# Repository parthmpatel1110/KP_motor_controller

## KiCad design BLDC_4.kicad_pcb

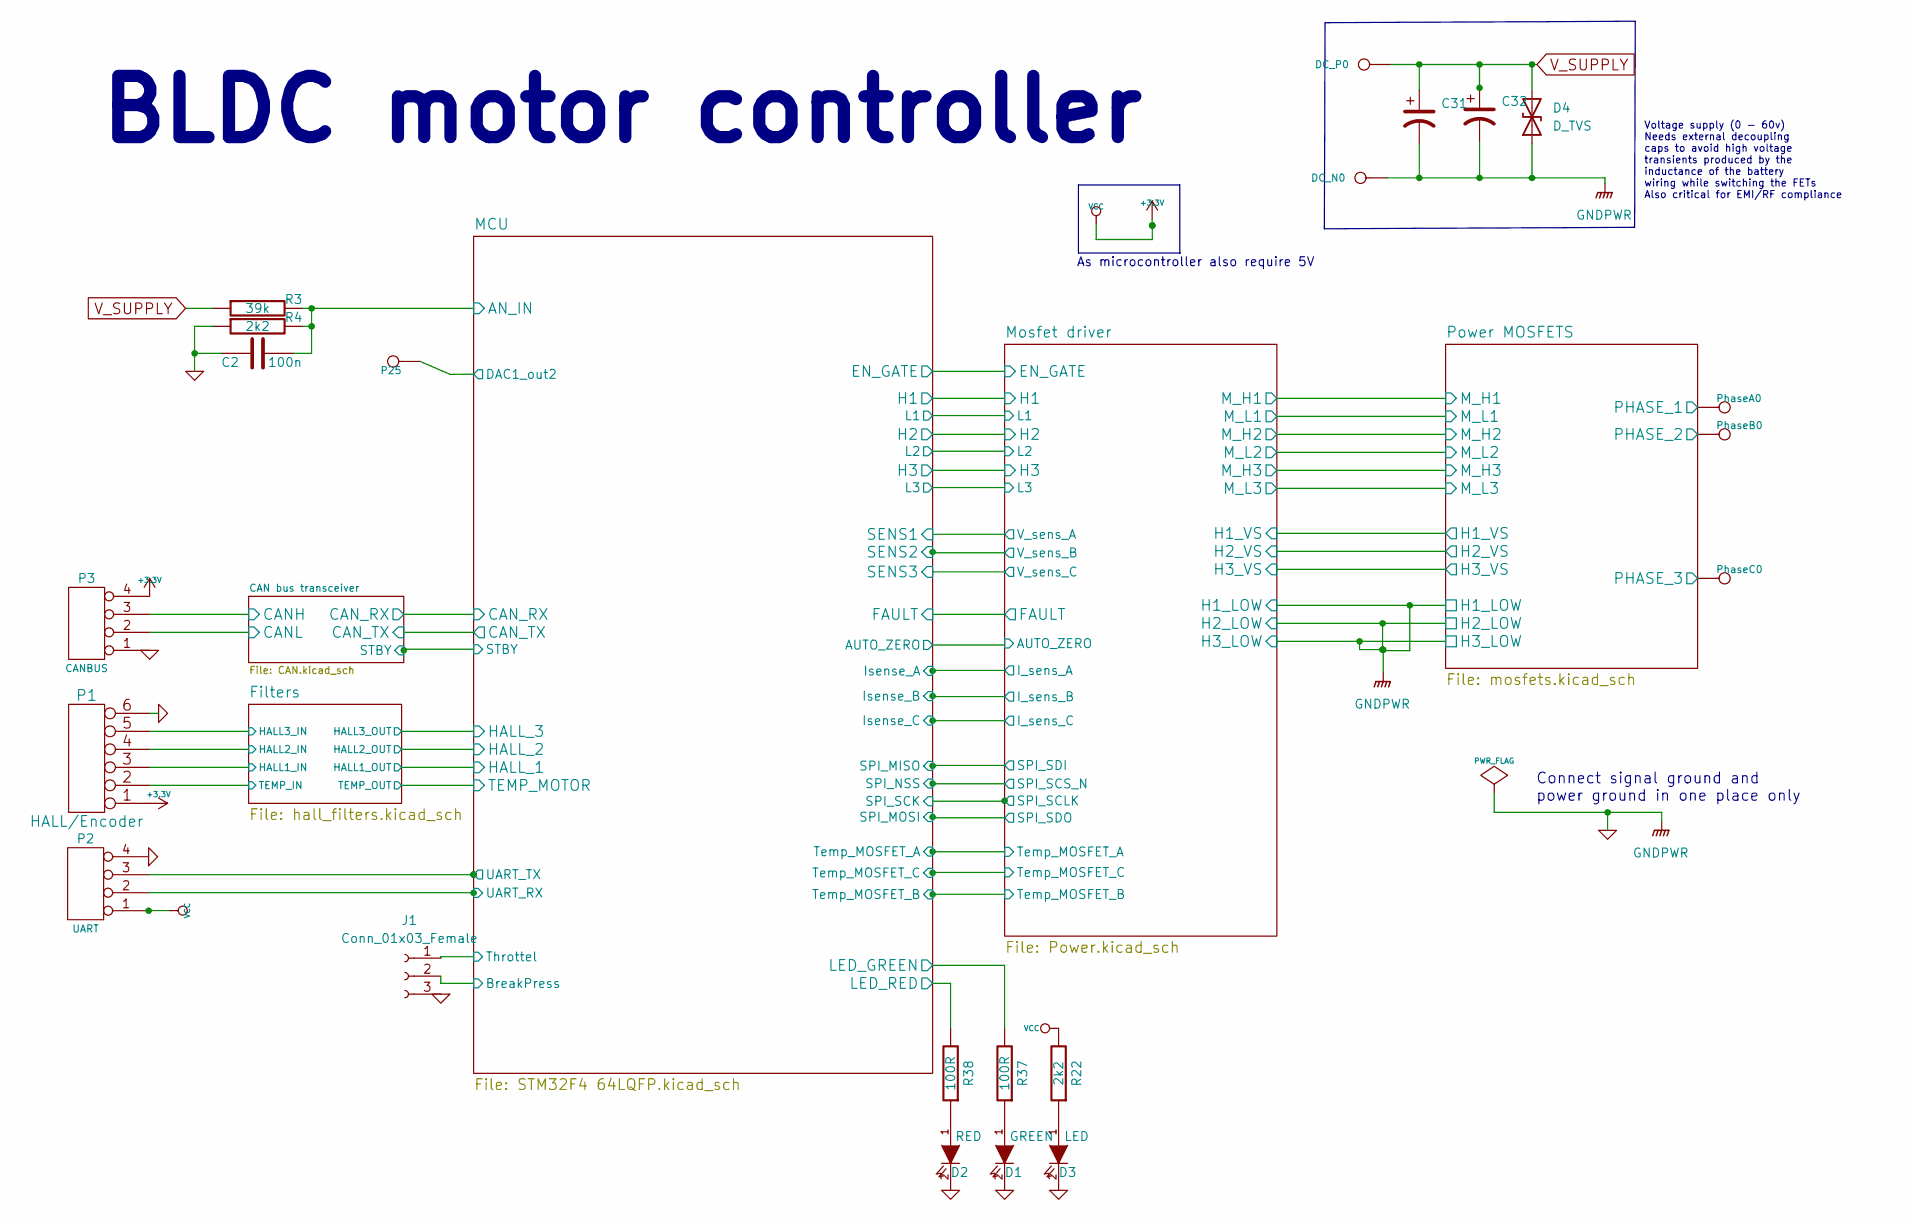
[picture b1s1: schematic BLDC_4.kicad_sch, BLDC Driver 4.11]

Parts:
C2: 100n; SMD-0603_c
C31, C32: C_Polarized_US; CAPAE1030X1270N
D1: GREEN; LED_0603_1608Metric
D2: RED; LED_0603_1608Metric
D3: LED; LED_0805_2012Metric
D4: D_TVS; DIOM5436X244N
DC_N0: IN-; 1PAD_4x5mm
DC_P0: IN+; 1PAD_4x5mm
J1: Conn_01x03_Female; SolderJumper-3_P1.3mm_Open_RoundedPad1.0x1.5mm_NumberLabels
P1: HALL/Encoder; MICRO_JST_6
P2: UART; JST_VH_B4P-VH-B_1x04_P3.96mm_Vertical
P3: CANBUS; JST_VH_B4P-VH-B_1x04_P3.96mm_Vertical
P25: MOTOR3; 1PAD_Small
PhaseA0: MOTOR3; 1PAD_4x5mm
PhaseB0: MOTOR2; 1PAD_4x5mm
PhaseC0: MOTOR1; 1PAD_4x5mm
R3: 39k; SMD-0603_r
R4, R22: 2k2; SMD-0603_r
R37, R38: 100R; SMD-0603_r

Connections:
/CAN bus transceiver/CANH: P3.3; also elsewhere on the board
/CAN bus transceiver/CANL: P3.2; also elsewhere on the board
/Filters/HALL1_IN: P1.3; also elsewhere on the board
/Filters/HALL2_IN: P1.4; also elsewhere on the board
/Filters/HALL3_IN: P1.5; also elsewhere on the board
/Filters/TEMP_MOTOR: P1.2; also elsewhere on the board
/MCU/AN_IN: C2.2, R3.2, R4.2; also elsewhere on the board
/MCU/BreakPress: J1.2; also elsewhere on the board
/MCU/DAC1_out2: P25.1; also elsewhere on the board
/MCU/LED_GREEN: R37.2; also elsewhere on the board
/MCU/LED_RED: R38.2; also elsewhere on the board
/MCU/Throttel: J1.1; also elsewhere on the board
/MCU/UART_RX: P2.2; also elsewhere on the board
/MCU/UART_TX: P2.3; also elsewhere on the board
/Mosfet driver/H1_VS: PhaseA0.1; also elsewhere on the board
/Mosfet driver/H2_VS: PhaseB0.1; also elsewhere on the board
/Mosfet driver/H3_VS: PhaseC0.1; also elsewhere on the board
GND: C2.1, C31.2, C32.2, D1.2 (K), D2.2 (K), D3.2 (K), D4.1 (A1), DC_N0.1, J1.3, P1.6, P2.4, P3.1, R4.1; also elsewhere on the board
unnamed: D1.1 (A), R37.1
unnamed: D2.1 (A), R38.1
unnamed: D3.1 (A), R22.1
V_SUPPLY: C31.1, C32.1, D4.2 (A2), DC_P0.1, R3.1; also elsewhere on the board

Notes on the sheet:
BLDC motor controller
Connect signal ground and power ground in one place only
As microcontroller also require 5V
Voltage supply (0 - 60v) Needs external decoupling caps to avoid high voltage transients produced by the inductance of the battery wiring while switching the FETs Also critical for EMI/RF compliance

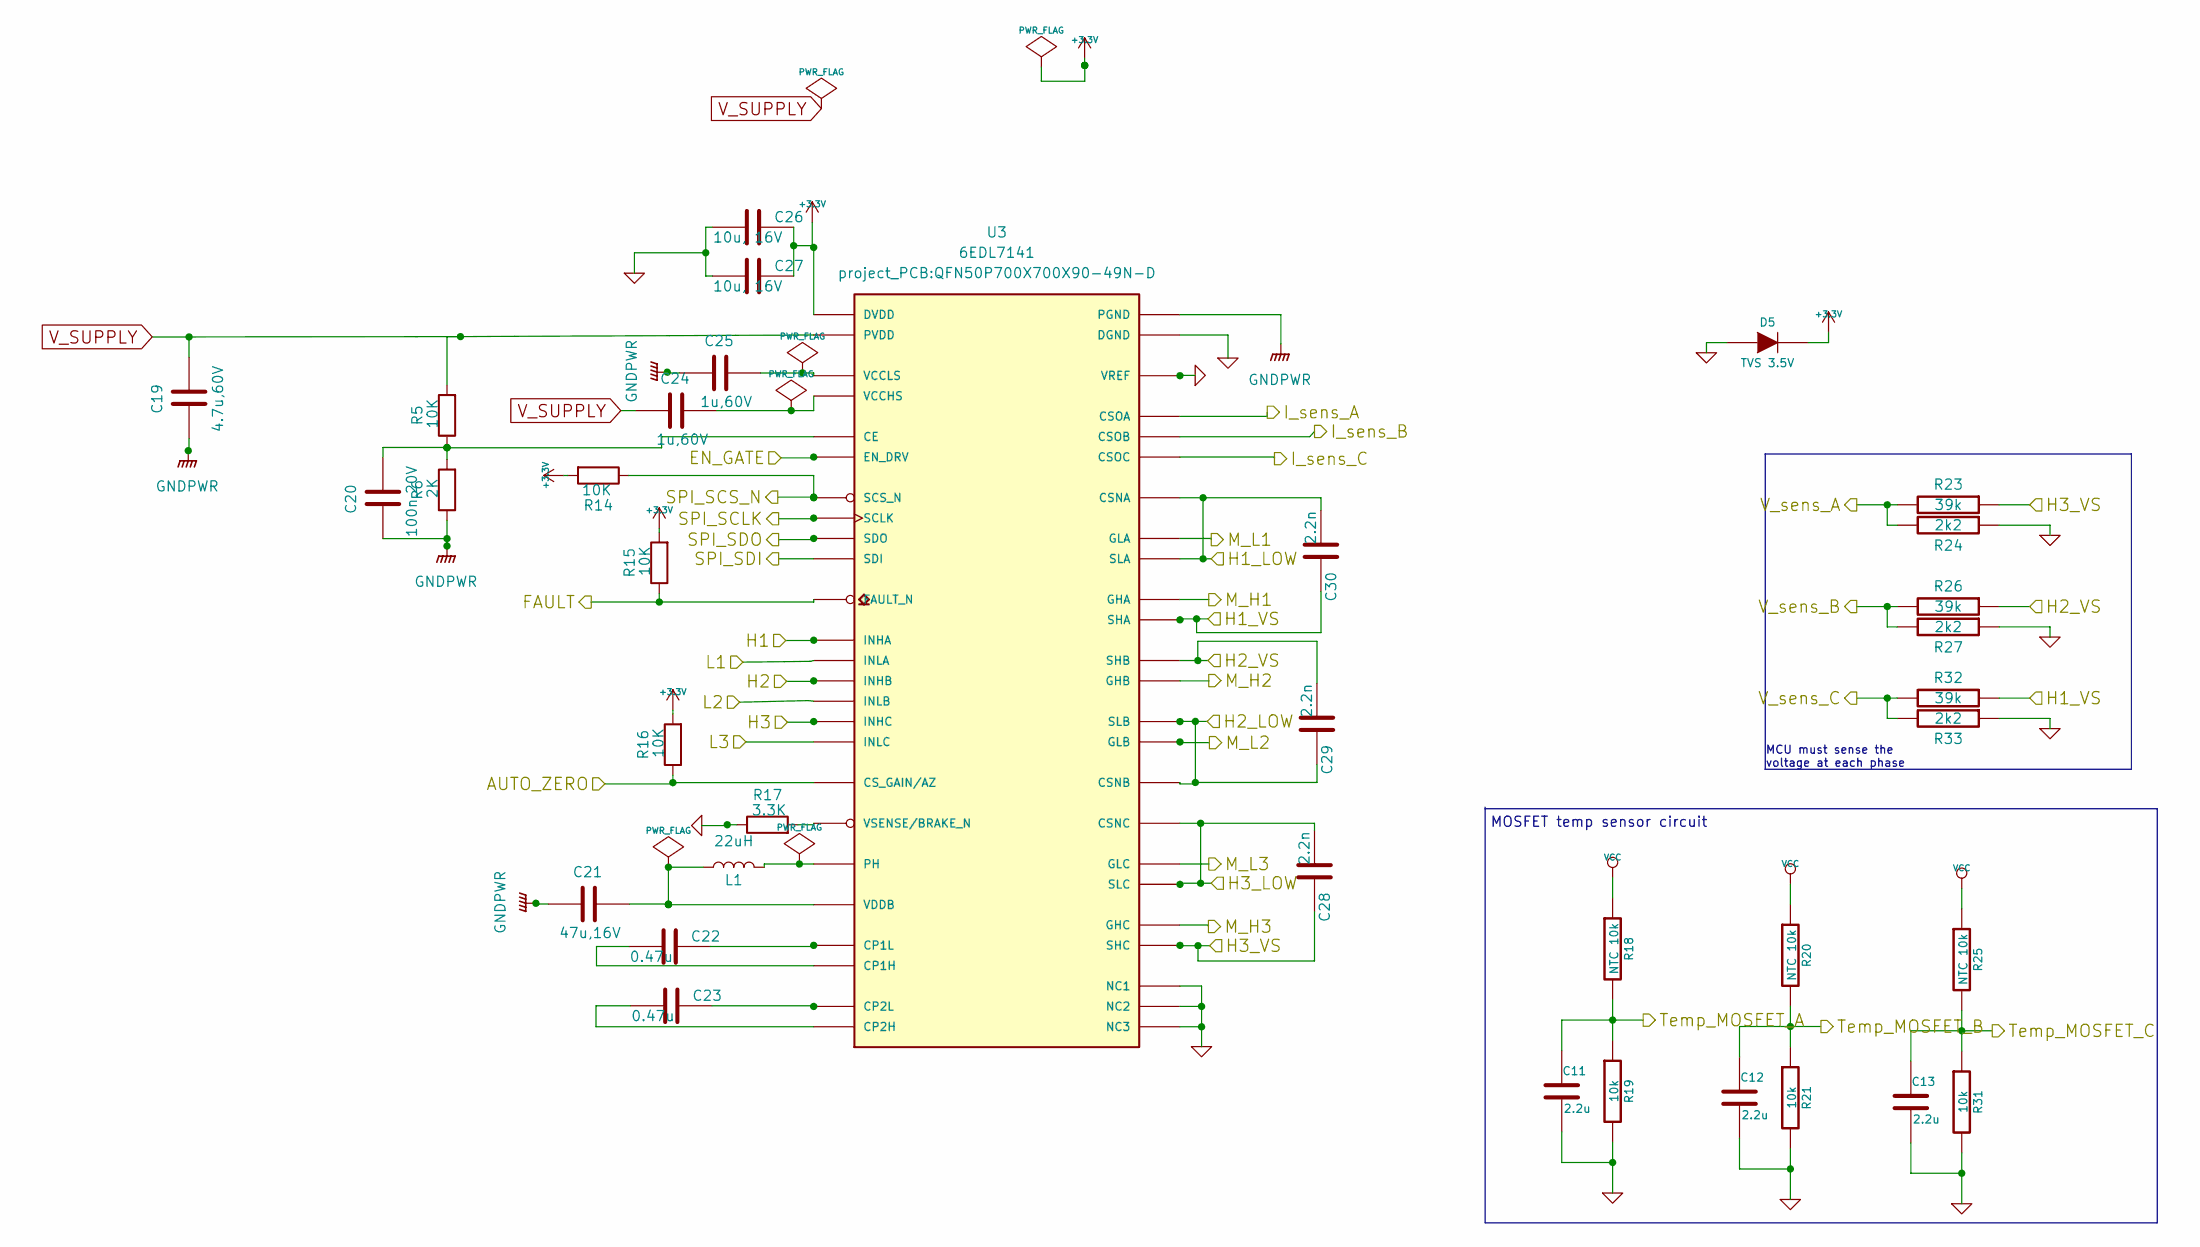
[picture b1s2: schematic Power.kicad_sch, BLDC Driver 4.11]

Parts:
C11, C12, C13: 2.2u; SMD-0603_c
C19: 4.7u,60V; SMD-0603_c
C20: 100n,20V; SMD-0603_c
C21: 47u,16V; SMD-1206
C22, C23: 0.47u; SMD-0603_c
C24, C25: 1u,60V; SMD-1206
C26, C27: 10u, 16V; SMD-0603_c
C28, C29, C30: 2.2n; SMD-0603_c
D5: TVS 3.5V; D_SMA
L1: 22uH; inductor_smd_MP002867
R5, R14, R15, R16: 10K; SMD-0603_r
R6: 2K; SMD-0603_r
R17: 3.3K; SMD-0603_r
R18, R20, R25: NTC 10k; SMD-0603_r
R19, R21, R31: 10k; SMD-0603_r
R23, R26, R32: 39k; SMD-0603_r
R24, R27, R33: 2k2; SMD-0603_r
U3: 6EDL7141; QFN50P700X700X90-49N-D

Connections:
/MCU/AUTO_ZERO: R16.1, U3.12 (CS_GAIN/AZ); also elsewhere on the board
/MCU/EN_GATE: U3.48 (EN_DRV); also elsewhere on the board
/MCU/FAULT: R15.1, U3.5 (FAULT_N); also elsewhere on the board
/MCU/H1: U3.6 (INHA); also elsewhere on the board
/MCU/H2: U3.8 (INHB); also elsewhere on the board
/MCU/H3: U3.10 (INHC); also elsewhere on the board
/MCU/Isense_A: U3.43 (CSOA); also elsewhere on the board
/MCU/Isense_B: U3.44 (CSOB); also elsewhere on the board
/MCU/Isense_C: U3.45 (CSOC); also elsewhere on the board
/MCU/L1: U3.7 (INLA); also elsewhere on the board
/MCU/L2: U3.9 (INLB); also elsewhere on the board
/MCU/L3: U3.11 (INLC); also elsewhere on the board
/MCU/SENS1: R23.2, R24.2; also elsewhere on the board
/MCU/SENS2: R26.2, R27.2; also elsewhere on the board
/MCU/SENS3: R32.2, R33.2; also elsewhere on the board
/MCU/SPI_MISO: U3.4 (SDI); also elsewhere on the board
/MCU/SPI_MOSI: U3.3 (SDO); also elsewhere on the board
/MCU/SPI_NSS: R14.1, U3.1 (SCS_N); also elsewhere on the board
/MCU/SPI_SCK: U3.2 (SCLK); also elsewhere on the board
/MCU/Temp_MOSFET_A: C11.1, R18.2, R19.1; also elsewhere on the board
/MCU/Temp_MOSFET_B: C12.1, R20.2, R21.1; also elsewhere on the board
/MCU/Temp_MOSFET_C: C13.1, R25.2, R31.1; also elsewhere on the board
/Mosfet driver/H1_VS: C30.1, R32.1, U3.38 (SHA); also elsewhere on the board
/Mosfet driver/H2_VS: C29.2, R26.1, U3.35 (SHB); also elsewhere on the board
/Mosfet driver/H3_VS: C28.1, R23.1, U3.26 (SHC); also elsewhere on the board
/Mosfet driver/M_H1: U3.37 (GHA); also elsewhere on the board
/Mosfet driver/M_H2: U3.36 (GHB); also elsewhere on the board
/Mosfet driver/M_H3: U3.25 (GHC); also elsewhere on the board
/Mosfet driver/M_L1: U3.40 (GLA); also elsewhere on the board
/Mosfet driver/M_L2: U3.33 (GLB); also elsewhere on the board
/Mosfet driver/M_L3: U3.28 (GLC); also elsewhere on the board
GND: C11.2, C12.2, C13.2, C19.1, C20.1, C21.1, C25.1, C26.2, C27.2, C28.2, C29.1, C30.2, D5.1 (A), R6.1, R17.1, R19.2, R21.2, R24.1, R27.1, R31.2, R33.1, U3.17 (PGND), U3.27 (NC1), U3.29 (SLC), U3.30 (CSNC), U3.31 (CSNB), U3.32 (SLB), U3.34 (NC2), U3.39 (NC3), U3.41 (SLA), U3.42 (CSNA), U3.46 (VREF), U3.49 (DGND); also elsewhere on the board
unnamed: C20.2, R5.1, R6.2, U3.47 (CE)
unnamed: C21.2, L1.1, U3.18 (VDDB)
unnamed: C22.1, U3.19 (CP1L)
unnamed: C22.2, U3.20 (CP1H)
unnamed: C23.1, U3.21 (CP2L)
unnamed: C23.2, U3.22 (CP2H)
unnamed: C24.2, U3.24 (VCCHS)
unnamed: C25.2, U3.23 (VCCLS)
unnamed: L1.2, U3.16 (PH)
unnamed: R17.2, U3.13 (VSENSE/BRAKE_N)
V_SUPPLY: C19.2, C24.1, R5.2, U3.15 (PVDD); also elsewhere on the board

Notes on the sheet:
MCU must sense the voltage at each phase
MOSFET temp sensor circuit

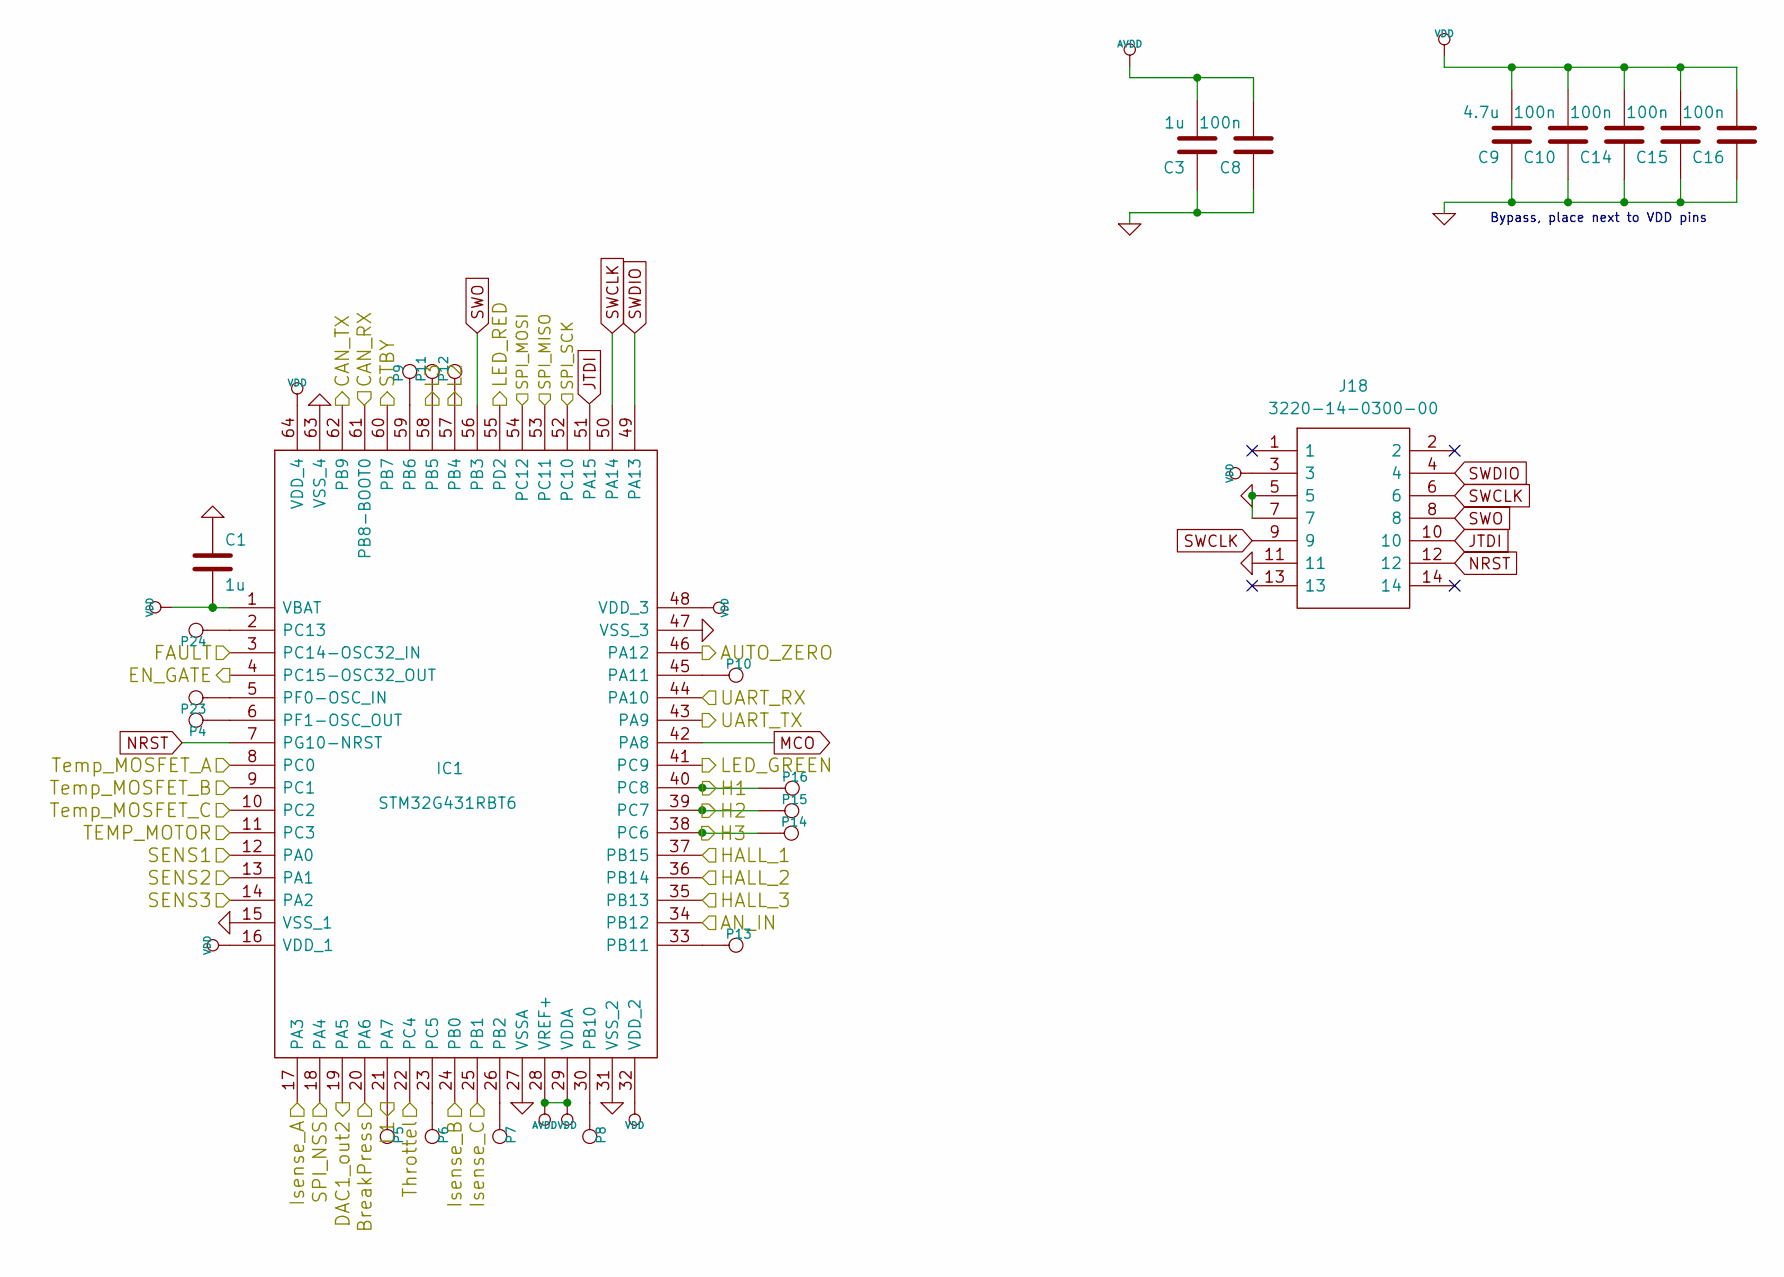
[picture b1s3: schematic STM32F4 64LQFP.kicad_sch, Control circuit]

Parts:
C1, C3: 1u; SMD-0603_c
C8, C10, C14, C15, C16: 100n; SMD-0603_c
C9: 4.7u; SMD-0603_c
IC1: STM32G431RBT6; QFP50P1200X1200X160-64N; Manufacturer_Part_Number STM32G431RBT6; Mouser Part Number 511-STM32G431RBT6
J18: 3220-14-0300-00; 322014030000; Manufacturer_Part_Number 3220-14-0300-00
P4, P5, P6, P7, P8, P9, P10, P11, P12, P13, P14, P15, P16, P23, P24: MOTOR3; 1PAD_Small

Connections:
/CAN bus transceiver/CAN_RX: IC1.61 (PB8-BOOT0); also elsewhere on the board
/CAN bus transceiver/CAN_TX: IC1.62 (PB9); also elsewhere on the board
/CAN bus transceiver/STBY: IC1.60 (PB7); also elsewhere on the board
/Filters/HALL1_OUT: IC1.37 (PB15); also elsewhere on the board
/Filters/HALL2_OUT: IC1.36 (PB14); also elsewhere on the board
/Filters/HALL3_OUT: IC1.35 (PB13); also elsewhere on the board
/Filters/TEMP_MOTOR: IC1.11 (PC3); also elsewhere on the board
/MCU/AN_IN: IC1.34 (PB12); also elsewhere on the board
/MCU/AUTO_ZERO: IC1.46 (PA12); also elsewhere on the board
/MCU/BreakPress: IC1.20 (PA6); also elsewhere on the board
/MCU/DAC1_out2: IC1.19 (PA5); also elsewhere on the board
/MCU/EN_GATE: IC1.4 (PC15-OSC32_OUT); also elsewhere on the board
/MCU/FAULT: IC1.3 (PC14-OSC32_IN); also elsewhere on the board
/MCU/H1: IC1.40 (PC8), P16.1; also elsewhere on the board
/MCU/H2: IC1.39 (PC7), P15.1; also elsewhere on the board
/MCU/H3: IC1.38 (PC6), P14.1; also elsewhere on the board
/MCU/Isense_A: IC1.17 (PA3); also elsewhere on the board
/MCU/Isense_B: IC1.24 (PB0); also elsewhere on the board
/MCU/Isense_C: IC1.25 (PB1); also elsewhere on the board
/MCU/L1: IC1.21 (PA7), P5.1; also elsewhere on the board
/MCU/L2: IC1.57 (PB4), P12.1; also elsewhere on the board
/MCU/L3: IC1.58 (PB5), P11.1; also elsewhere on the board
/MCU/LED_GREEN: IC1.41 (PC9); also elsewhere on the board
/MCU/LED_RED: IC1.55 (PD2); also elsewhere on the board
/MCU/SENS1: IC1.12 (PA0); also elsewhere on the board
/MCU/SENS2: IC1.13 (PA1); also elsewhere on the board
/MCU/SENS3: IC1.14 (PA2); also elsewhere on the board
/MCU/SPI_MISO: IC1.53 (PC11); also elsewhere on the board
/MCU/SPI_MOSI: IC1.54 (PC12); also elsewhere on the board
/MCU/SPI_NSS: IC1.18 (PA4); also elsewhere on the board
/MCU/SPI_SCK: IC1.52 (PC10); also elsewhere on the board
/MCU/Temp_MOSFET_A: IC1.8 (PC0); also elsewhere on the board
/MCU/Temp_MOSFET_B: IC1.9 (PC1); also elsewhere on the board
/MCU/Temp_MOSFET_C: IC1.10 (PC2); also elsewhere on the board
/MCU/Throttel: IC1.22 (PC4); also elsewhere on the board
/MCU/UART_RX: IC1.44 (PA10); also elsewhere on the board
/MCU/UART_TX: IC1.43 (PA9); also elsewhere on the board
GND: C1.1, C3.1, C8.1, C9.1, C10.1, C14.1, C15.1, C16.1, IC1.15 (VSS_1), IC1.27 (VSSA), IC1.31 (VSS_2), IC1.47 (VSS_3), IC1.63 (VSS_4), J18.5, J18.7, J18.11; also elsewhere on the board
JTDI: IC1.51 (PA15), J18.10
MCO: IC1.42 (PA8)
NRST: IC1.7 (PG10-NRST), J18.12
unnamed: IC1.2 (PC13), P24.1
unnamed: IC1.5 (PF0-OSC_IN), P23.1
unnamed: IC1.6 (PF1-OSC_OUT), P4.1
unnamed: IC1.23 (PC5), P6.1
unnamed: IC1.26 (PB2), P7.1
unnamed: IC1.30 (PB10), P8.1
unnamed: IC1.33 (PB11), P13.1
unnamed: IC1.45 (PA11), P10.1
unnamed: IC1.59 (PB6), P9.1
SWCLK: IC1.50 (PA14), J18.6, J18.9
SWDIO: IC1.49 (PA13), J18.4
SWO: IC1.56 (PB3), J18.8

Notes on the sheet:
Bypass, place next to VDD pins

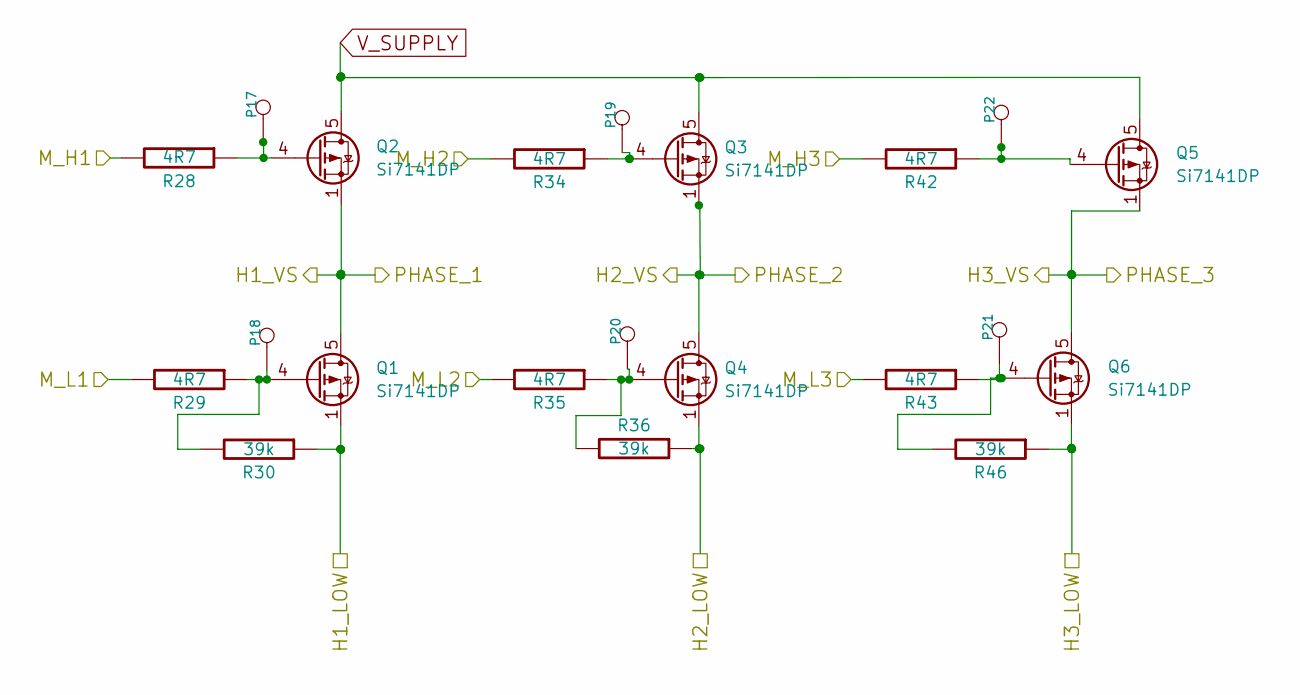
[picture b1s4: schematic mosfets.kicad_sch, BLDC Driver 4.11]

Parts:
P17, P18, P19, P20, P21, P22: MOTOR3; 1PAD_Small
Q1, Q2, Q3, Q4, Q5, Q6: Si7141DP; PowerPAK_SO-8_Single
R28, R29, R34, R35, R42, R43: 4R7; SMD-0603_r
R30, R36, R46: 39k; SMD-0603_r

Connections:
/Mosfet driver/H1_VS: Q1.5 (D), Q2.1 (S), Q2.2 (S), Q2.3 (S); also elsewhere on the board
/Mosfet driver/H2_VS: Q3.1 (S), Q3.2 (S), Q3.3 (S), Q4.5 (D); also elsewhere on the board
/Mosfet driver/H3_VS: Q5.1 (S), Q5.2 (S), Q5.3 (S), Q6.5 (D); also elsewhere on the board
/Mosfet driver/M_H1: R28.2; also elsewhere on the board
/Mosfet driver/M_H2: R34.2; also elsewhere on the board
/Mosfet driver/M_H3: R42.2; also elsewhere on the board
/Mosfet driver/M_L1: R29.2; also elsewhere on the board
/Mosfet driver/M_L2: R35.2; also elsewhere on the board
/Mosfet driver/M_L3: R43.2; also elsewhere on the board
GND: Q1.1 (S), Q1.2 (S), Q1.3 (S), Q4.1 (S), Q4.2 (S), Q4.3 (S), Q6.1 (S), Q6.2 (S), Q6.3 (S), R30.1, R36.1, R46.1; also elsewhere on the board
unnamed: P17.1, Q2.4 (G), R28.1
unnamed: P18.1, Q1.4 (G), R29.1, R30.2
unnamed: P19.1, Q3.4 (G), R34.1
unnamed: P20.1, Q4.4 (G), R35.1, R36.2
unnamed: P21.1, Q6.4 (G), R43.1, R46.2
unnamed: P22.1, Q5.4 (G), R42.1
V_SUPPLY: Q2.5 (D), Q3.5 (D), Q5.5 (D); also elsewhere on the board

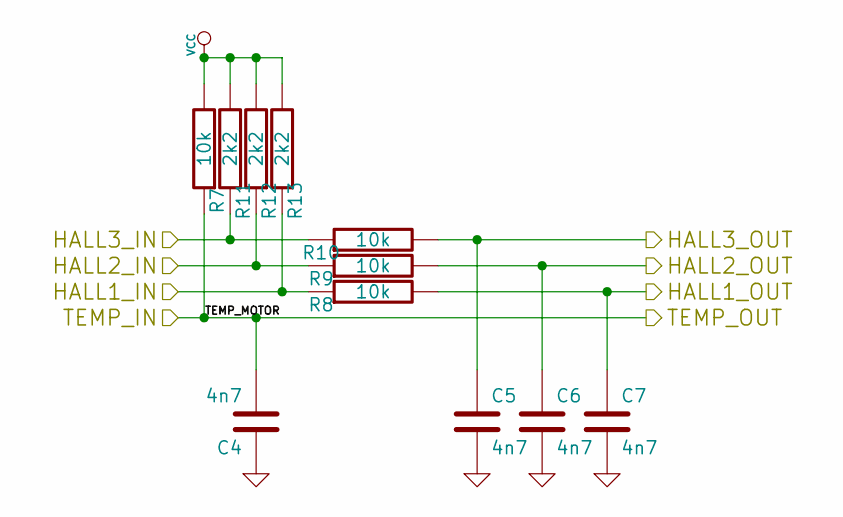
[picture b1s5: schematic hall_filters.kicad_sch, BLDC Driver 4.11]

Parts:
C4, C5, C6, C7: 4n7; SMD-0603_c
R7, R8, R9, R10: 10k; SMD-0603_r
R11, R12, R13: 2k2; SMD-0603_r

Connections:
/Filters/HALL1_IN: R8.1, R13.1; also elsewhere on the board
/Filters/HALL1_OUT: C7.1, R8.2; also elsewhere on the board
/Filters/HALL2_IN: R9.1, R12.1; also elsewhere on the board
/Filters/HALL2_OUT: C6.1, R9.2; also elsewhere on the board
/Filters/HALL3_IN: R10.1, R11.1; also elsewhere on the board
/Filters/HALL3_OUT: C5.1, R10.2; also elsewhere on the board
/Filters/TEMP_MOTOR: C4.2, R7.1; also elsewhere on the board
GND: C4.1, C5.2, C6.2, C7.2; also elsewhere on the board

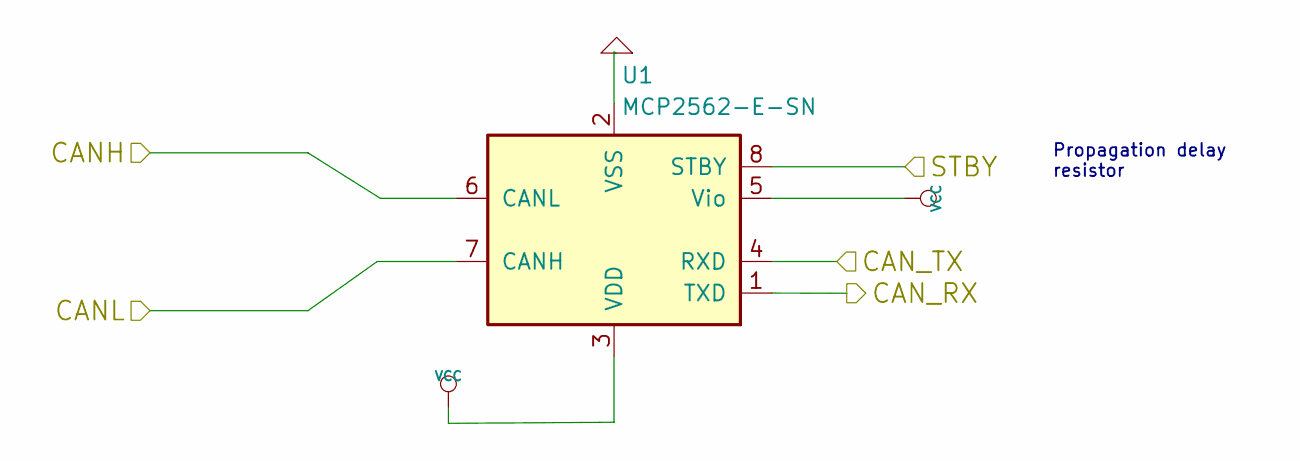
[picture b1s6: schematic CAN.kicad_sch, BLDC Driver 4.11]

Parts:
U1: MCP2562-E-SN; SOIC-8_3.9x4.9mm_P1.27mm

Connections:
/CAN bus transceiver/CANH: U1.6 (CANL); also elsewhere on the board
/CAN bus transceiver/CANL: U1.7 (CANH); also elsewhere on the board
/CAN bus transceiver/CAN_RX: U1.1 (TXD); also elsewhere on the board
/CAN bus transceiver/CAN_TX: U1.4 (RXD); also elsewhere on the board
/CAN bus transceiver/STBY: U1.8 (STBY); also elsewhere on the board
GND: U1.2 (VSS); also elsewhere on the board

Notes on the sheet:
Propagation delay resistor

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
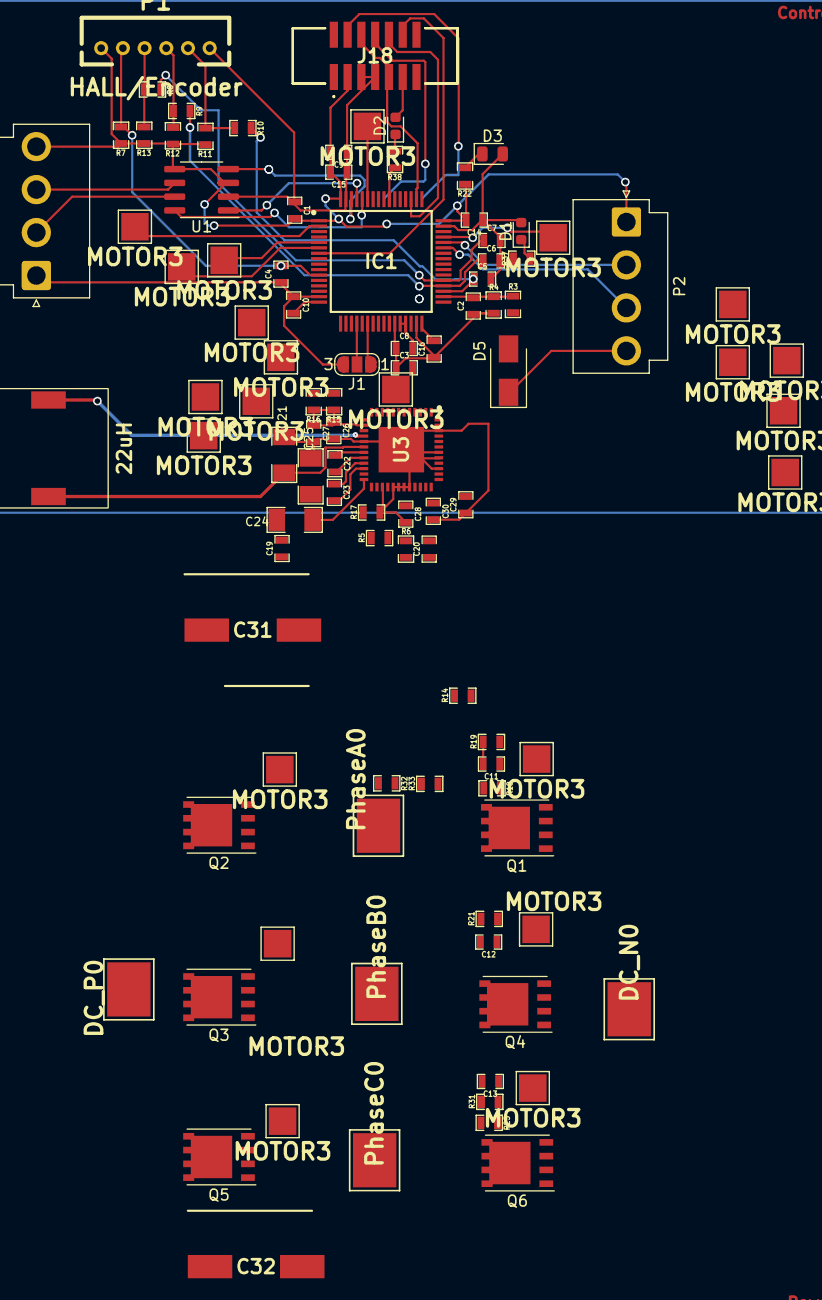
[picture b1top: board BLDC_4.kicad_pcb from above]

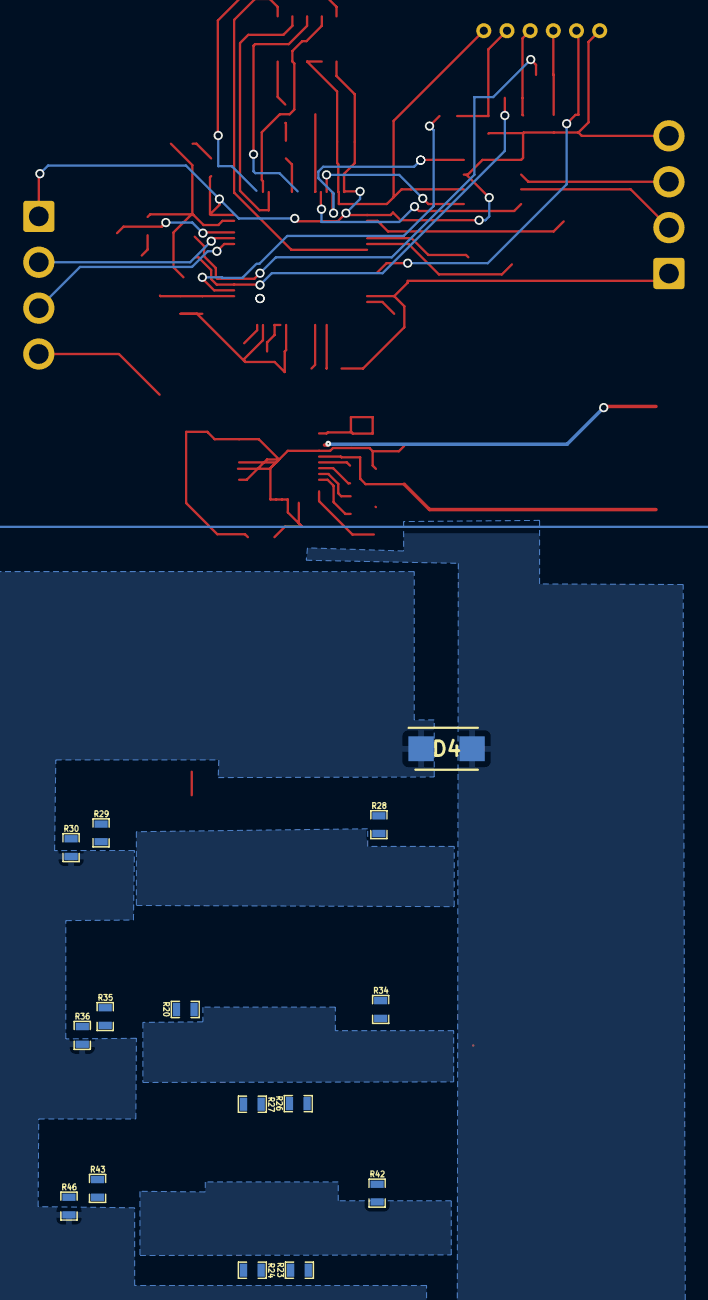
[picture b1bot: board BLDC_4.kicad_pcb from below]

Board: 2 copper layers, 116 parts (15 on the bottom side), 87 nets.

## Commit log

2023-03-13 Schematic done. Working toward PCB layout in kicad.
